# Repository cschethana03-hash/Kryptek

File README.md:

# Kryptek

Kryptek is my custom full size (108 key) wireless mechanical keyboard, its built around an **Adafruit Feather nRF52840 Express**.

so basicaly i wanted a full size board that could work wireles over bluetooth but still be usable as a normal wired keyboard when i need it too, and i wanted to understand the entire thing instead of just putting together a kit.. the matrix, the diodes, the I2C gpio expanders, the battery, the screen, the leds ALL of it, so i designed the whole thing from scratch in kicad and fusion 360 which took a ridiculous amount of time lol

## why i made this

im 17 and i spend a stupid amount of time on a keyboard for school, coding and basically everything else.. so i thought if im going to use one this much i might aswell build one that i actualy understand from the switch all the way down to the firmware

main goals i set for myself :

- design a full size PCB in kicad (108 keys, nav cluster and numpad included)
- make it **wireless** with bluetooth and a lipo battery, but keep usb-c for wired use
- scan the whole key matrix through I2C GPIO expanders
- add a 1.9" LCD for a custom animated status screen
- add separate caps lock, num lock, battery low and charging status indicators
- design a proper printable case, plate and bottom parts in fusion 360
- learn the full pipeline : schematic -> pcb -> 3d model -> case -> firmware

the hardest parts were fitting a full size matrix, the usb and display wiring, and getting all the little status features to coexist with the keyboard scan.. but seeing the complete layout and case come together made it worth it

## project status

this repo has the complete hardware design, cad files, firmware and manufacturing outputs. its basically a complete V1 build, although there are definitely things i would change if i make a V2

whats included :

- kicad project, schematic and pcb
- full fusion 360 design and `.step` export
- printable case parts (`.stl`) and plate
- production files (bom, positions, designators, ipc netlist and gerber zip)
- KMK / CircuitPython firmware for the nRF52840
- schematic and layout PDFs

current hardware summary :

| | |
|---|---|
| Layout | full size, 108 keys (main block + nav + numpad) |
| Controller | Adafruit Feather nRF52840 Express |
| Connectivity | bluetooth LE **and** USB-C wired mode (Fn+Esc toggles at runtime) |
| Matrix | 21 columns x 6 rows, scanned through 2x MCP23017 I2C expanders |
| Diodes | 1N4148W, one per switch (COL2ROW) |
| Battery | 500mAh 1S LiPo with battery voltage monitoring |
| Display | Waveshare 1.9" ST7789 IPS LCD |
| Indicators | Caps Lock, Num Lock, battery low and charging status LEDs |
| Stabilizers | MX compatible stabilizers for the large keys |
| Switches | MX compatible mechanical switches |
| Keycaps | Plum Blossom cherry profile shine-through PBT |
| Case | 3d printed custom case designed in Fusion 360 |
| PCB | custom PCB with production files included |

the case is mostly a clean white shell with the kryptek branding built into the design, and the blue display / indicator area gives it the little bit of personality i wanted without making the board look too busy

## images

### full 3d model

### top case and layout

### pcb

### pcb 3d view

### schematic / wiring
the matrix, both gpio expanders, the mcu, usb-c, esd protection, stabilizers, leds and display connector are all documented in the schematic..

### display and status indicators

### other case screenshots

## repo file checklist

important files in this repo :

- `PCB/Kryptek.kicad_pro`
- `PCB/Kryptek.kicad_sch`
- `PCB/Kryptek.kicad_pcb`
- `CAD/Full/Kryptek.step`
- `Fusion/Kryptek.f3d`
- `CAD/Printing/`  -> `Plate.stl`, `Top Plate.stl`, `Bottom.stl`, `Bottom Lifter.stl`, `Bottom Lifter Screw.stl`
- `Firmware/Firmware.py`
- `Production/bom.csv`
- `Production/positions.csv`
- `Production/designators.csv`
- `Production/netlist.ipc`
- `Production/Kryptek.zip`  (gerbers)
- `bom.csv`
- `PDF/Kryptek.pdf`  (schematic print)
- `PDF/Kryptek-Layout.pdf`  (keyboard layout / drawing)

## cad

designed in **fusion 360**.. the editable design is in `Fusion/Kryptek.f3d` and theres a `.step` export in `CAD/Full/` if you just want the geometry. all the print ready parts are in `CAD/Printing/`

the case includes the top plate, bottom shell, bottom lifter and lifter screw parts, so the complete printable enclosure is kept together with the project instead of being only a render

## firmware note

firmware is **KMK** running on **CircuitPython**, and its all in one file :

- `Firmware/Firmware.py`

it has the nRF52840 Feather pin map, two MCP23017 expanders at `0x20` and `0x21`, the full 108 key matrix, the lock and battery led logic, the ST7789 display setup and the animated cherry blossom scene. the peripheral code is wrapped in try/except so if a display or led is missing it should still let you type instead of completely stopping

to flash it : double tap RESET on the feather, copy the CircuitPython `.uf2` if needed, then copy `Firmware.py` plus the `kmk/` folder and the required `lib/` drivers (`adafruit_mcp230xx`, `adafruit_bus_device`, `adafruit_ble`, `adafruit_st7789`, `adafruit_display_text`) onto the `CIRCUITPY` drive

by defalt it boots as **usb** so its easy to test during first bring up, and **Fn+Esc** switches over to bluetooth. if you want bluetooth first just swap `hid_type` and `secondary_hid_type` at the bottom of `Firmware.py`

## bom (summary)

full bom is in `bom.csv`. the original prices are in usd and the current INR fields are left blank for now

| # | Name | Purpose | Qty | Cost ($) | Distributor | Link |
|---|------|---------|-----|----------|-------------|------|
| 1 | 3D printed Case | keyboard case | 1 | 8.00 | Hack Club | [Buy](https://printlegion.hackclub.com) |
| 2 | PCB fabrication | the main board | 1 | 132.16 | LionCircuits | [Buy](https://www.lioncircuits.com/quote) |
| 3 | Plum Blossom Cherry Profile Top Shine-Through PBT Keycap Set V2 | keycaps to actualy type on | 1 | 28.11 | Curiosity Caps | [Buy](https://curiositycaps.in/products/plum-blossom-cherry-profile-shine-through-dye-sublimation-pbt-keycap-set) |
| 4 | Durock Clear Screw-In Stabilizers V2 | stabalizers for the big keys | 1 | 24.62 | Stackskb | [Buy](https://stackskb.com/store/durock-clear-screw-in-stabilizers-v2/?attribute_combination=7%2B1+Set&attribute_spacebar-size=6.25U) |
| 5 | Akko V3 Penguin Pro Switch (Pack of 45) | switches for the keys | 3 | 49.95 | Stackskb | [Buy](https://stackskb.com/store/hmx-volume-0-pack-of-35/) |
| 6 | Adafruit Feather nRF52840 Express | microcontroler / the brains | 1 | 63.69 | Robu | [Buy](https://robu.in/product/adafruit-feather-nrf52840-sense/) |
| 7 | WLY752530 3.7V 500mAh 1S LiPo Battery | battery | 1 | 1.71 | Robu | [Buy](https://robu.in/product/50mah-pcm-protected-micro-li-po-battery/) |
| 8 | 1N4148W SOD-123 Diode | diode (one per switch) | 216 | 1.59 | Robu | [Buy](https://robu.in/product/1n4148w-sod-123-1206-diodereel-of-3000/) |
| 9 | MCP23017-E/SO I/O expander | gpio expander | 4 | 8.78 | Robu | [Buy](https://robu.in/product/mcp23017-e-so-microchip-i-o-expander-16-bit-i2c-serial-1-8-v-5-5-v-soic-28-pins/) |
| 10 | Waveshare 1.9 inch LCD Display Module | the screen | 1 | 11.17 | Robu | [Buy](https://robu.in/product/waveshare-lcd-display-module-spi-interface-262k-colors/) |
| 11 | Lano Dark Blue Gx16 Aviator Connector 3.5m Cable | wired keyboard cable | 1 | 16.64 | Curiosity Caps | [Buy](https://curiositycaps.in/products/dark-blue-cable-black-connector-cable) |

the smaller capacitors, resistors, leds, usb connector, jst connector and protection parts are also listed in the full `bom.csv`

**total bom cost : $350.582**

---

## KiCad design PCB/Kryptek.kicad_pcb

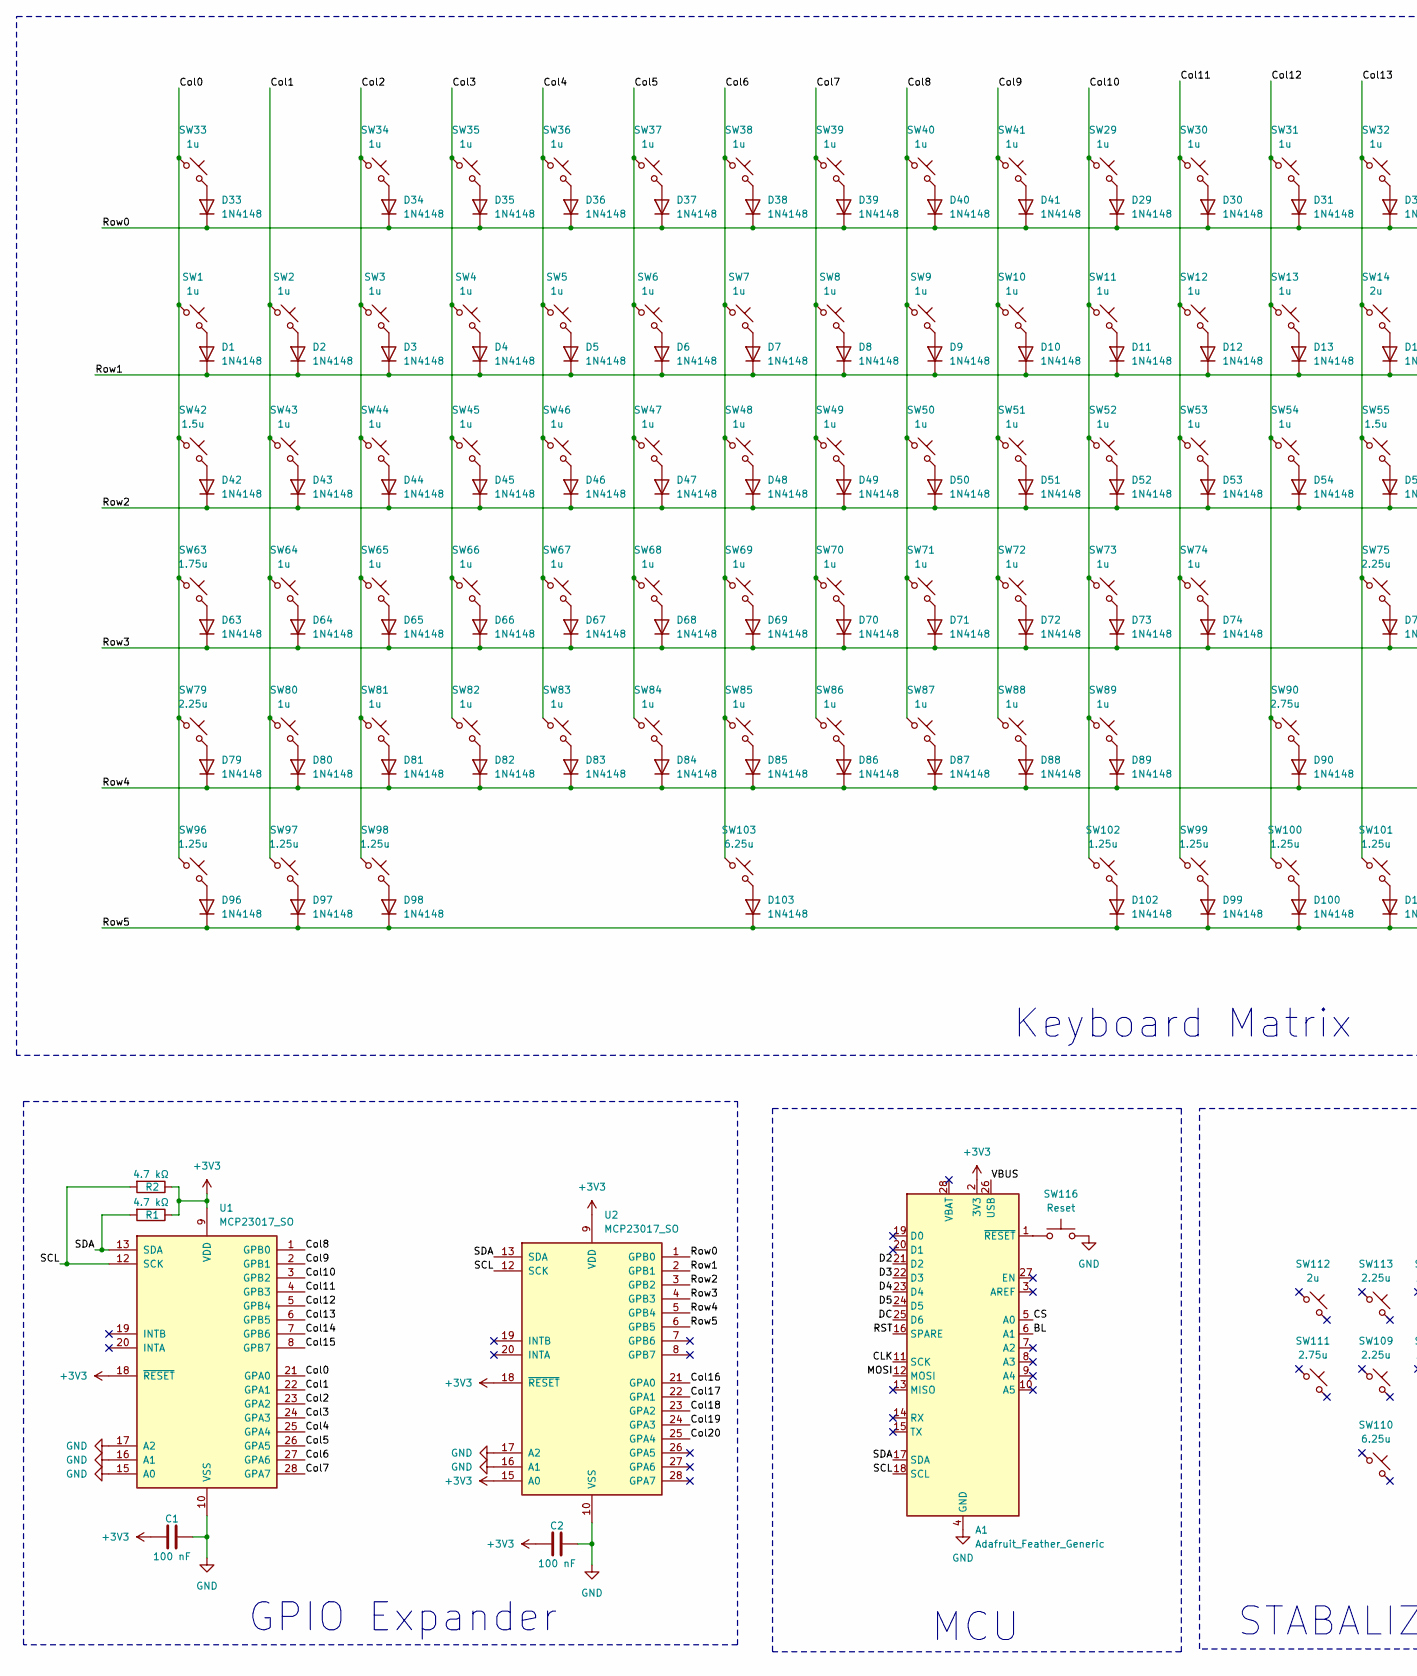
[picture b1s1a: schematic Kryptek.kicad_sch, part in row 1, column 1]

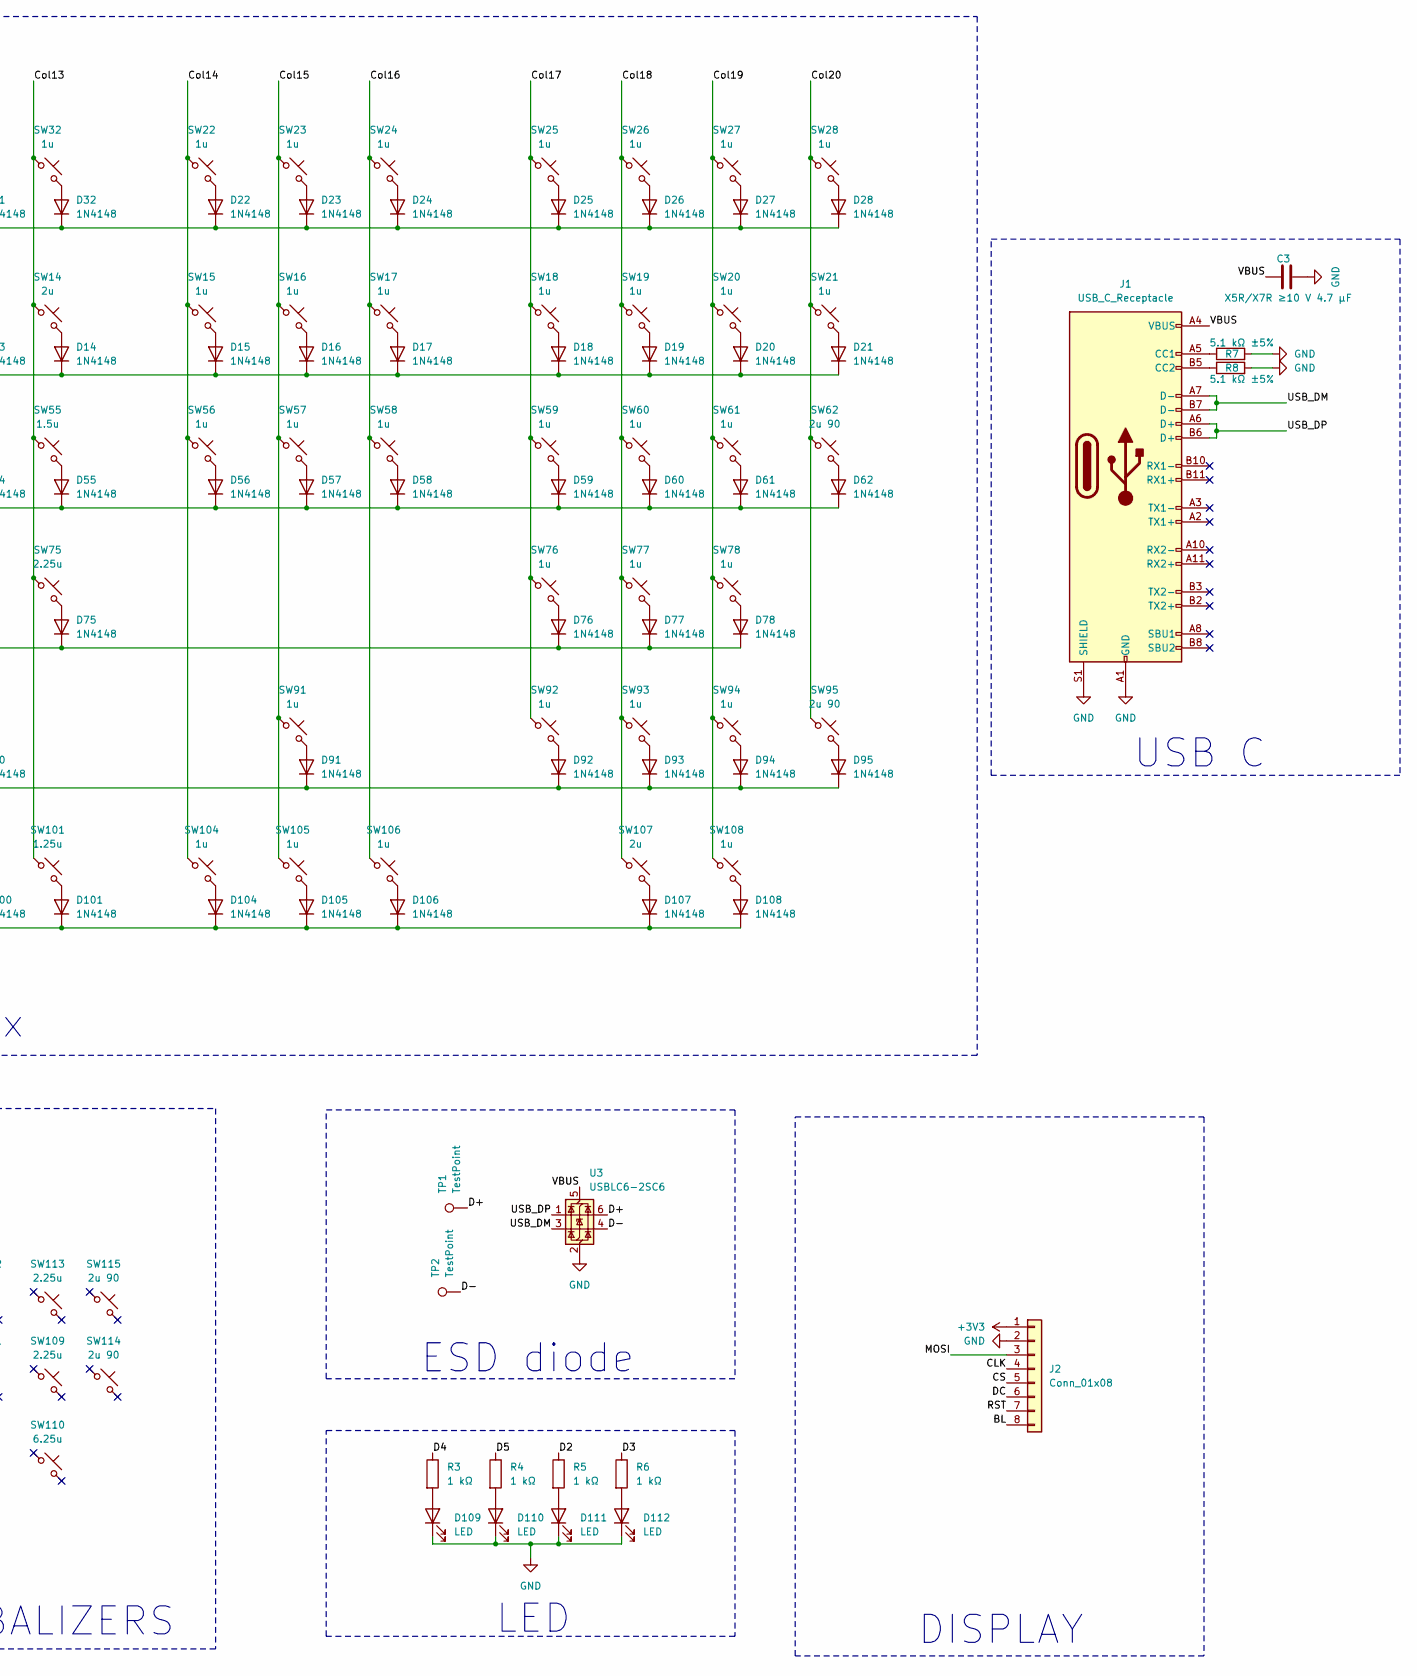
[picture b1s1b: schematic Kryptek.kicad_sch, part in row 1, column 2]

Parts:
A1: Adafruit_Feather_Generic; Adafruit_Feather_WithMountingHoles
C1, C2: 100 nF; C_0805_2012Metric
C3: X5R/X7R ≥10 V 4.7 µF; C_0805_2012Metric
D1, D2, D3, D4, D5, D6, D7, D8, D9, D10, D11, D12, D13, D14, D15, D16, D17, D18, D19, D20, D21, D22, D23, D24, D25, D26, D27, D28, D29, D30, D31, D32, D33, D34, D35, D36, D37, D38, D39, D40, D41, D42, D43, D44, D45, D46, D47, D48, D49, D50, D51, D52, D53, D54, D55, D56, D57, D58, D59, D60, D61, D62, D63, D64, D65, D66, D67, D68, D69, D70, D71, D72, D73, D74, D75, D76, D77, D78, D79, D80, D81, D82, D83, D84, D85, D86, D87, D88, D89, D90, D91, D92, D93, D94, D95, D96, D97, D98, D99, D100, D101, D102, D103, D104, D105, D106, D107, D108: 1N4148; D_SOD-123
D109, D110, D111, D112: LED; LED_D3.0mm
J1: USB_C_Receptacle; USB_C_Receptacle_HRO_TYPE-C-31-M-12
J2: Conn_01x08; JST_SH_SM08B-SRSS-TB_1x08-1MP_P1.00mm_Horizontal
R1, R2: 4.7 kΩ; R_0805_2012Metric
R3, R4, R5, R6: 1 kΩ; R_0805_2012Metric
R7, R8: 5.1 kΩ ±5%; R_0805_2012Metric
SW1, SW2, SW3, SW4, SW5, SW6, SW7, SW8, SW9, SW10, SW11, SW12, SW13, SW15, SW16, SW17, SW18, SW19, SW20, SW21, SW22, SW23, SW24, SW25, SW26, SW27, SW28, SW29, SW30, SW31, SW32, SW33, SW34, SW35, SW36, SW37, SW38, SW39, SW40, SW41, SW43, SW44, SW45, SW46, SW47, SW48, SW49, SW50, SW51, SW52, SW53, SW54, SW56, SW57, SW58, SW59, SW60, SW61, SW64, SW65, SW66, SW67, SW68, SW69, SW70, SW71, SW72, SW73, SW74, SW76, SW77, SW78, SW80, SW81, SW82, SW83, SW84, SW85, SW86, SW87, SW88, SW89, SW91, SW92, SW93, SW94, SW104, SW105, SW106, SW108: 1u; SW_Cherry_MX_PCB_1.00u
SW14, SW107: 2u; SW_Cherry_MX_PCB_2.00u
SW42, SW55: 1.5u; SW_Cherry_MX_PCB_1.50u
SW62, SW95: 2u 90; SW_Cherry_MX_PCB_2.00u_90deg
SW63: 1.75u; SW_Cherry_MX_PCB_1.75u
SW75, SW79: 2.25u; SW_Cherry_MX_PCB_2.25u
SW90: 2.75u; SW_Cherry_MX_PCB_2.75u
SW96, SW97, SW98, SW99, SW100, SW101, SW102: 1.25u; SW_Cherry_MX_PCB_1.25u
SW103: 6.25u; SW_Cherry_MX_Plate_6.25u
SW109, SW113: 2.25u; STAB_MX_2.25u
SW110: 6.25u; STAB_MX_6.25u
SW111: 2.75u; STAB_MX_2.75u
SW112: 2u; STAB_MX_2u
SW114, SW115: 2u 90; STAB_MX_2u
SW116: Reset; SW_PUSH_6mm
TP1, TP2: TestPoint; TestPoint_THTPad_D2.0mm_Drill1.0mm
U1, U2: MCP23017_SO; SOIC-28W_7.5x17.9mm_P1.27mm
U3: USBLC6-2SC6; SOT-23-6

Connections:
+3V3: A1.2 (3V3), C1.2, C2.2, J2.1, R1.1, R2.1, U1.9 (VDD), U1.18 (~RESET), U2.9 (VDD), U2.15 (A0), U2.18 (~RESET)
/BL: A1.6 (A1), J2.8
/CLK: A1.11 (SCK), J2.4
/CS: A1.5 (A0), J2.5
/Col0: SW1.1, SW33.1, SW42.1, SW63.1, SW79.1, SW96.1, U1.21 (GPA0)
/Col1: SW2.1, SW43.1, SW64.1, SW80.1, SW97.1, U1.22 (GPA1)
/Col2: SW3.1, SW34.1, SW44.1, SW65.1, SW81.1, SW98.1, U1.23 (GPA2)
/Col3: SW4.1, SW35.1, SW45.1, SW66.1, SW82.1, U1.24 (GPA3)
/Col4: SW5.1, SW36.1, SW46.1, SW67.1, SW83.1, U1.25 (GPA4)
/Col5: SW6.1, SW37.1, SW47.1, SW68.1, SW84.1, U1.26 (GPA5)
/Col6: SW7.1, SW38.1, SW48.1, SW69.1, SW85.1, SW103.1, U1.27 (GPA6)
/Col7: SW8.1, SW39.1, SW49.1, SW70.1, SW86.1, U1.28 (GPA7)
/Col8: SW9.1, SW40.1, SW50.1, SW71.1, SW87.1, U1.1 (GPB0)
/Col9: SW10.1, SW41.1, SW51.1, SW72.1, SW88.1, U1.2 (GPB1)
/Col10: SW11.1, SW29.1, SW52.1, SW73.1, SW89.1, SW102.1, U1.3 (GPB2)
/Col11: SW12.1, SW30.1, SW53.1, SW74.1, SW99.1, U1.4 (GPB3)
/Col12: SW13.1, SW31.1, SW54.1, SW90.1, SW100.1, U1.5 (GPB4)
/Col13: SW14.1, SW32.1, SW55.1, SW75.1, SW101.1, U1.6 (GPB5)
/Col14: SW15.1, SW22.1, SW56.1, SW104.1, U1.7 (GPB6)
/Col15: SW16.1, SW23.1, SW57.1, SW91.1, SW105.1, U1.8 (GPB7)
/Col16: SW17.1, SW24.1, SW58.1, SW106.1, U2.21 (GPA0)
/Col17: SW18.1, SW25.1, SW59.1, SW76.1, SW92.1, U2.22 (GPA1)
/Col18: SW19.1, SW26.1, SW60.1, SW77.1, SW93.1, SW107.1, U2.23 (GPA2)
/Col19: SW20.1, SW27.1, SW61.1, SW78.1, SW94.1, SW108.1, U2.24 (GPA3)
/Col20: SW21.1, SW28.1, SW62.1, SW95.1, U2.25 (GPA4)
/D2: A1.21 (D2), R5.1
/D3: A1.22 (D3), R6.1
/D4: A1.23 (D4), R3.1
/D5: A1.24 (D5), R4.1
/D+: TP1.1, U3.6 (I/O1)
/DC: A1.25 (D6), J2.6
/D−: TP2.1, U3.4 (I/O2)
/MOSI: A1.12 (MOSI), J2.3
/RST: A1.16 (SPARE), J2.7
/Row0: D22.1 (K), D23.1 (K), D24.1 (K), D25.1 (K), D26.1 (K), D27.1 (K), D28.1 (K), D29.1 (K), D30.1 (K), D31.1 (K), D32.1 (K), D33.1 (K), D34.1 (K), D35.1 (K), D36.1 (K), D37.1 (K), D38.1 (K), D39.1 (K), D40.1 (K), D41.1 (K), U2.1 (GPB0)
/Row1: D1.1 (K), D2.1 (K), D3.1 (K), D4.1 (K), D5.1 (K), D6.1 (K), D7.1 (K), D8.1 (K), D9.1 (K), D10.1 (K), D11.1 (K), D12.1 (K), D13.1 (K), D14.1 (K), D15.1 (K), D16.1 (K), D17.1 (K), D18.1 (K), D19.1 (K), D20.1 (K), D21.1 (K), U2.2 (GPB1)
/Row2: D42.1 (K), D43.1 (K), D44.1 (K), D45.1 (K), D46.1 (K), D47.1 (K), D48.1 (K), D49.1 (K), D50.1 (K), D51.1 (K), D52.1 (K), D53.1 (K), D54.1 (K), D55.1 (K), D56.1 (K), D57.1 (K), D58.1 (K), D59.1 (K), D60.1 (K), D61.1 (K), D62.1 (K), U2.3 (GPB2)
/Row3: D63.1 (K), D64.1 (K), D65.1 (K), D66.1 (K), D67.1 (K), D68.1 (K), D69.1 (K), D70.1 (K), D71.1 (K), D72.1 (K), D73.1 (K), D74.1 (K), D75.1 (K), D76.1 (K), D77.1 (K), D78.1 (K), U2.4 (GPB3)
/Row4: D79.1 (K), D80.1 (K), D81.1 (K), D82.1 (K), D83.1 (K), D84.1 (K), D85.1 (K), D86.1 (K), D87.1 (K), D88.1 (K), D89.1 (K), D90.1 (K), D91.1 (K), D92.1 (K), D93.1 (K), D94.1 (K), D95.1 (K), U2.5 (GPB4)
/Row5: D96.1 (K), D97.1 (K), D98.1 (K), D99.1 (K), D100.1 (K), D101.1 (K), D102.1 (K), D103.1 (K), D104.1 (K), D105.1 (K), D106.1 (K), D107.1 (K), D108.1 (K), U2.6 (GPB5)
/SCL: A1.18 (SCL), R2.2, U1.12 (SCK), U2.12 (SCK)
/SDA: A1.17 (SDA), R1.2, U1.13 (SDA), U2.13 (SDA)
/USB_DM: J1.A7 (D-), J1.B7 (D-), U3.3 (I/O2)
/USB_DP: J1.A6 (D+), J1.B6 (D+), U3.1 (I/O1)
/VBUS: A1.26 (USB), C3.1, J1.A4 (VBUS), J1.A9 (VBUS), J1.B4 (VBUS), J1.B9 (VBUS), U3.5 (VBUS)
GND: A1.4 (GND), C1.1, C2.1, C3.2, D109.1 (K), D110.1 (K), D111.1 (K), D112.1 (K), J1.A1 (GND), J1.A12 (GND), J1.B1 (GND), J1.B12 (GND), J1.S1 (SHIELD), J2.2, R7.2, R8.2, SW116.2, U1.10 (VSS), U1.15 (A0), U1.16 (A1), U1.17 (A2), U2.10 (VSS), U2.16 (A1), U2.17 (A2), U3.2 (GND)
unnamed: A1.1 (~RESET), SW116.1
unnamed: D1.2 (A), SW1.2
unnamed: D2.2 (A), SW2.2
unnamed: D3.2 (A), SW3.2
unnamed: D4.2 (A), SW4.2
unnamed: D5.2 (A), SW5.2
unnamed: D6.2 (A), SW6.2
unnamed: D7.2 (A), SW7.2
unnamed: D8.2 (A), SW8.2
unnamed: D9.2 (A), SW9.2
unnamed: D10.2 (A), SW10.2
unnamed: D11.2 (A), SW11.2
unnamed: D12.2 (A), SW12.2
unnamed: D13.2 (A), SW13.2
unnamed: D14.2 (A), SW14.2
unnamed: D15.2 (A), SW15.2
unnamed: D16.2 (A), SW16.2
unnamed: D17.2 (A), SW17.2
unnamed: D18.2 (A), SW18.2
unnamed: D19.2 (A), SW19.2
unnamed: D20.2 (A), SW20.2
unnamed: D21.2 (A), SW21.2
unnamed: D22.2 (A), SW22.2
unnamed: D23.2 (A), SW23.2
unnamed: D24.2 (A), SW24.2
unnamed: D25.2 (A), SW25.2
unnamed: D26.2 (A), SW26.2
unnamed: D27.2 (A), SW27.2
unnamed: D28.2 (A), SW28.2
unnamed: D29.2 (A), SW29.2
unnamed: D30.2 (A), SW30.2
unnamed: D31.2 (A), SW31.2
unnamed: D32.2 (A), SW32.2
unnamed: D33.2 (A), SW33.2
unnamed: D34.2 (A), SW34.2
unnamed: D35.2 (A), SW35.2
unnamed: D36.2 (A), SW36.2
unnamed: D37.2 (A), SW37.2
unnamed: D38.2 (A), SW38.2
unnamed: D39.2 (A), SW39.2
unnamed: D40.2 (A), SW40.2
unnamed: D41.2 (A), SW41.2
unnamed: D42.2 (A), SW42.2
unnamed: D43.2 (A), SW43.2
unnamed: D44.2 (A), SW44.2
unnamed: D45.2 (A), SW45.2
unnamed: D46.2 (A), SW46.2
unnamed: D47.2 (A), SW47.2
unnamed: D48.2 (A), SW48.2
unnamed: D49.2 (A), SW49.2
unnamed: D50.2 (A), SW50.2
unnamed: D51.2 (A), SW51.2
unnamed: D52.2 (A), SW52.2
unnamed: D53.2 (A), SW53.2
unnamed: D54.2 (A), SW54.2
unnamed: D55.2 (A), SW55.2
unnamed: D56.2 (A), SW56.2
unnamed: D57.2 (A), SW57.2
unnamed: D58.2 (A), SW58.2
unnamed: D59.2 (A), SW59.2
unnamed: D60.2 (A), SW60.2
unnamed: D61.2 (A), SW61.2
unnamed: D62.2 (A), SW62.2
unnamed: D63.2 (A), SW63.2
unnamed: D64.2 (A), SW64.2
unnamed: D65.2 (A), SW65.2
unnamed: D66.2 (A), SW66.2
unnamed: D67.2 (A), SW67.2
unnamed: D68.2 (A), SW68.2
unnamed: D69.2 (A), SW69.2
unnamed: D70.2 (A), SW70.2
unnamed: D71.2 (A), SW71.2
unnamed: D72.2 (A), SW72.2
unnamed: D73.2 (A), SW73.2
unnamed: D74.2 (A), SW74.2
unnamed: D75.2 (A), SW75.2
unnamed: D76.2 (A), SW76.2
unnamed: D77.2 (A), SW77.2
unnamed: D78.2 (A), SW78.2
unnamed: D79.2 (A), SW79.2
unnamed: D80.2 (A), SW80.2
unnamed: D81.2 (A), SW81.2
unnamed: D82.2 (A), SW82.2
unnamed: D83.2 (A), SW83.2
unnamed: D84.2 (A), SW84.2
unnamed: D85.2 (A), SW85.2
unnamed: D86.2 (A), SW86.2
unnamed: D87.2 (A), SW87.2
unnamed: D88.2 (A), SW88.2
unnamed: D89.2 (A), SW89.2
unnamed: D90.2 (A), SW90.2
unnamed: D91.2 (A), SW91.2
unnamed: D92.2 (A), SW92.2
unnamed: D93.2 (A), SW93.2
unnamed: D94.2 (A), SW94.2
unnamed: D95.2 (A), SW95.2
unnamed: D96.2 (A), SW96.2
unnamed: D97.2 (A), SW97.2
unnamed: D98.2 (A), SW98.2
unnamed: D99.2 (A), SW99.2
unnamed: D100.2 (A), SW100.2
unnamed: D101.2 (A), SW101.2
unnamed: D102.2 (A), SW102.2
unnamed: D103.2 (A), SW103.2
unnamed: D104.2 (A), SW104.2
unnamed: D105.2 (A), SW105.2
unnamed: D106.2 (A), SW106.2
unnamed: D107.2 (A), SW107.2
unnamed: D108.2 (A), SW108.2
unnamed: D109.2 (A), R3.2
unnamed: D110.2 (A), R4.2
unnamed: D111.2 (A), R5.2
unnamed: D112.2 (A), R6.2
unnamed: J1.A5 (CC1), R7.1
unnamed: J1.B5 (CC2), R8.1

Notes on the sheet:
USB C
DISPLAY
STABALIZERS
GPIO Expander
ESD diode
Keyboard Matrix
MCU
LED

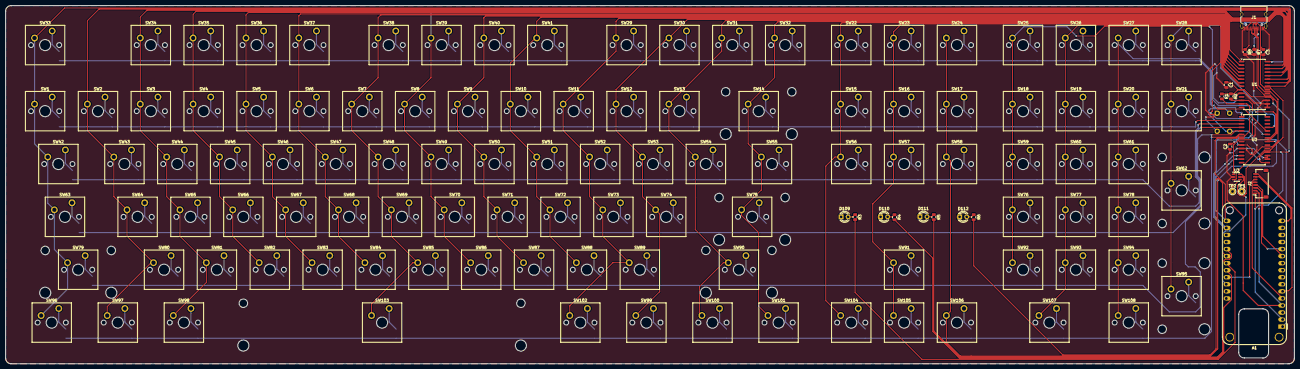
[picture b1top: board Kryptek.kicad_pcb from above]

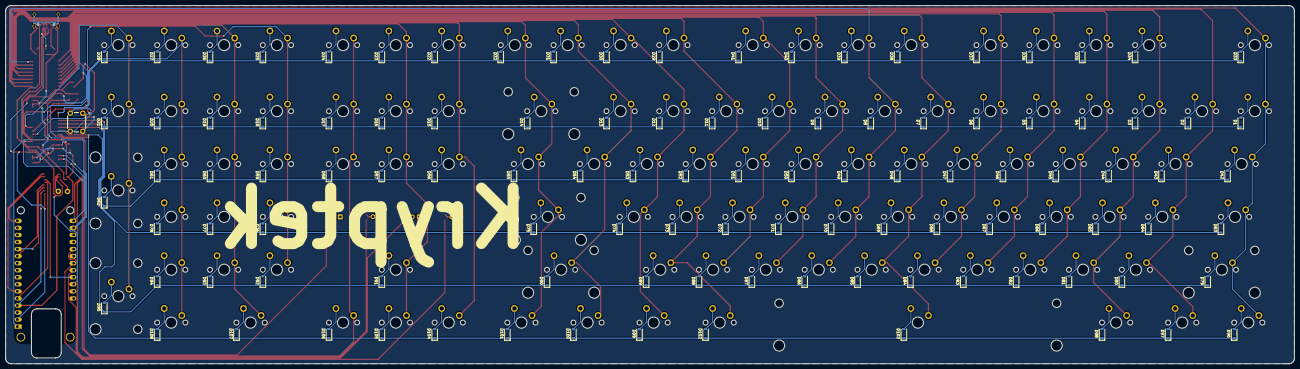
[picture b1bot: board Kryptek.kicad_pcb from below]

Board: 2 copper layers, 464.4 x 129.1 mm, 247 parts (109 on the bottom side), 161 nets.

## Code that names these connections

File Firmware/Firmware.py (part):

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
# get_pin(n): n = 0..7 -> GPA0..GPA7 ,  n = 8..15 -> GPB0..GPB7
col_pins = [
    mcp1.get_pin(0),  mcp1.get_pin(1),  mcp1.get_pin(2),  mcp1.get_pin(3),   # Col0-3   U1 GPA0-3
    mcp1.get_pin(4),  mcp1.get_pin(5),  mcp1.get_pin(6),  mcp1.get_pin(7),   # Col4-7   U1 GPA4-7
    mcp1.get_pin(8),  mcp1.get_pin(9),  mcp1.get_pin(10), mcp1.get_pin(11),  # Col8-11  U1 GPB0-3
    mcp1.get_pin(12), mcp1.get_pin(13), mcp1.get_pin(14), mcp1.get_pin(15),  # Col12-15 U1 GPB4-7
    mcp2.get_pin(0),  mcp2.get_pin(1),  mcp2.get_pin(2),  mcp2.get_pin(3),   # Col16-19 U2 GPA0-3
    mcp2.get_pin(4),                                                          # Col20    U2 GPA4
]
row_pins = [
    mcp2.get_pin(8),  mcp2.get_pin(9),  mcp2.get_pin(10),                     # Row0-2  U2 GPB0-2
    mcp2.get_pin(11), mcp2.get_pin(12), mcp2.get_pin(13),                     # Row3-5  U2 GPB3-5
]
COLS = len(col_pins)   # 21
ROWS = len(row_pins)   # 6
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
